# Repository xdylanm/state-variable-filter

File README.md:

# State Variable Filter

The state variable filter is a second order (12dB/oct) filter with low-, high- and band-pass outputs and adjustable resonance. This is a classic filter design that appears in a number of synths, including the Oberheim SEM.

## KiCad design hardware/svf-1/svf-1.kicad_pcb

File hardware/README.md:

Store hardware project and panel here

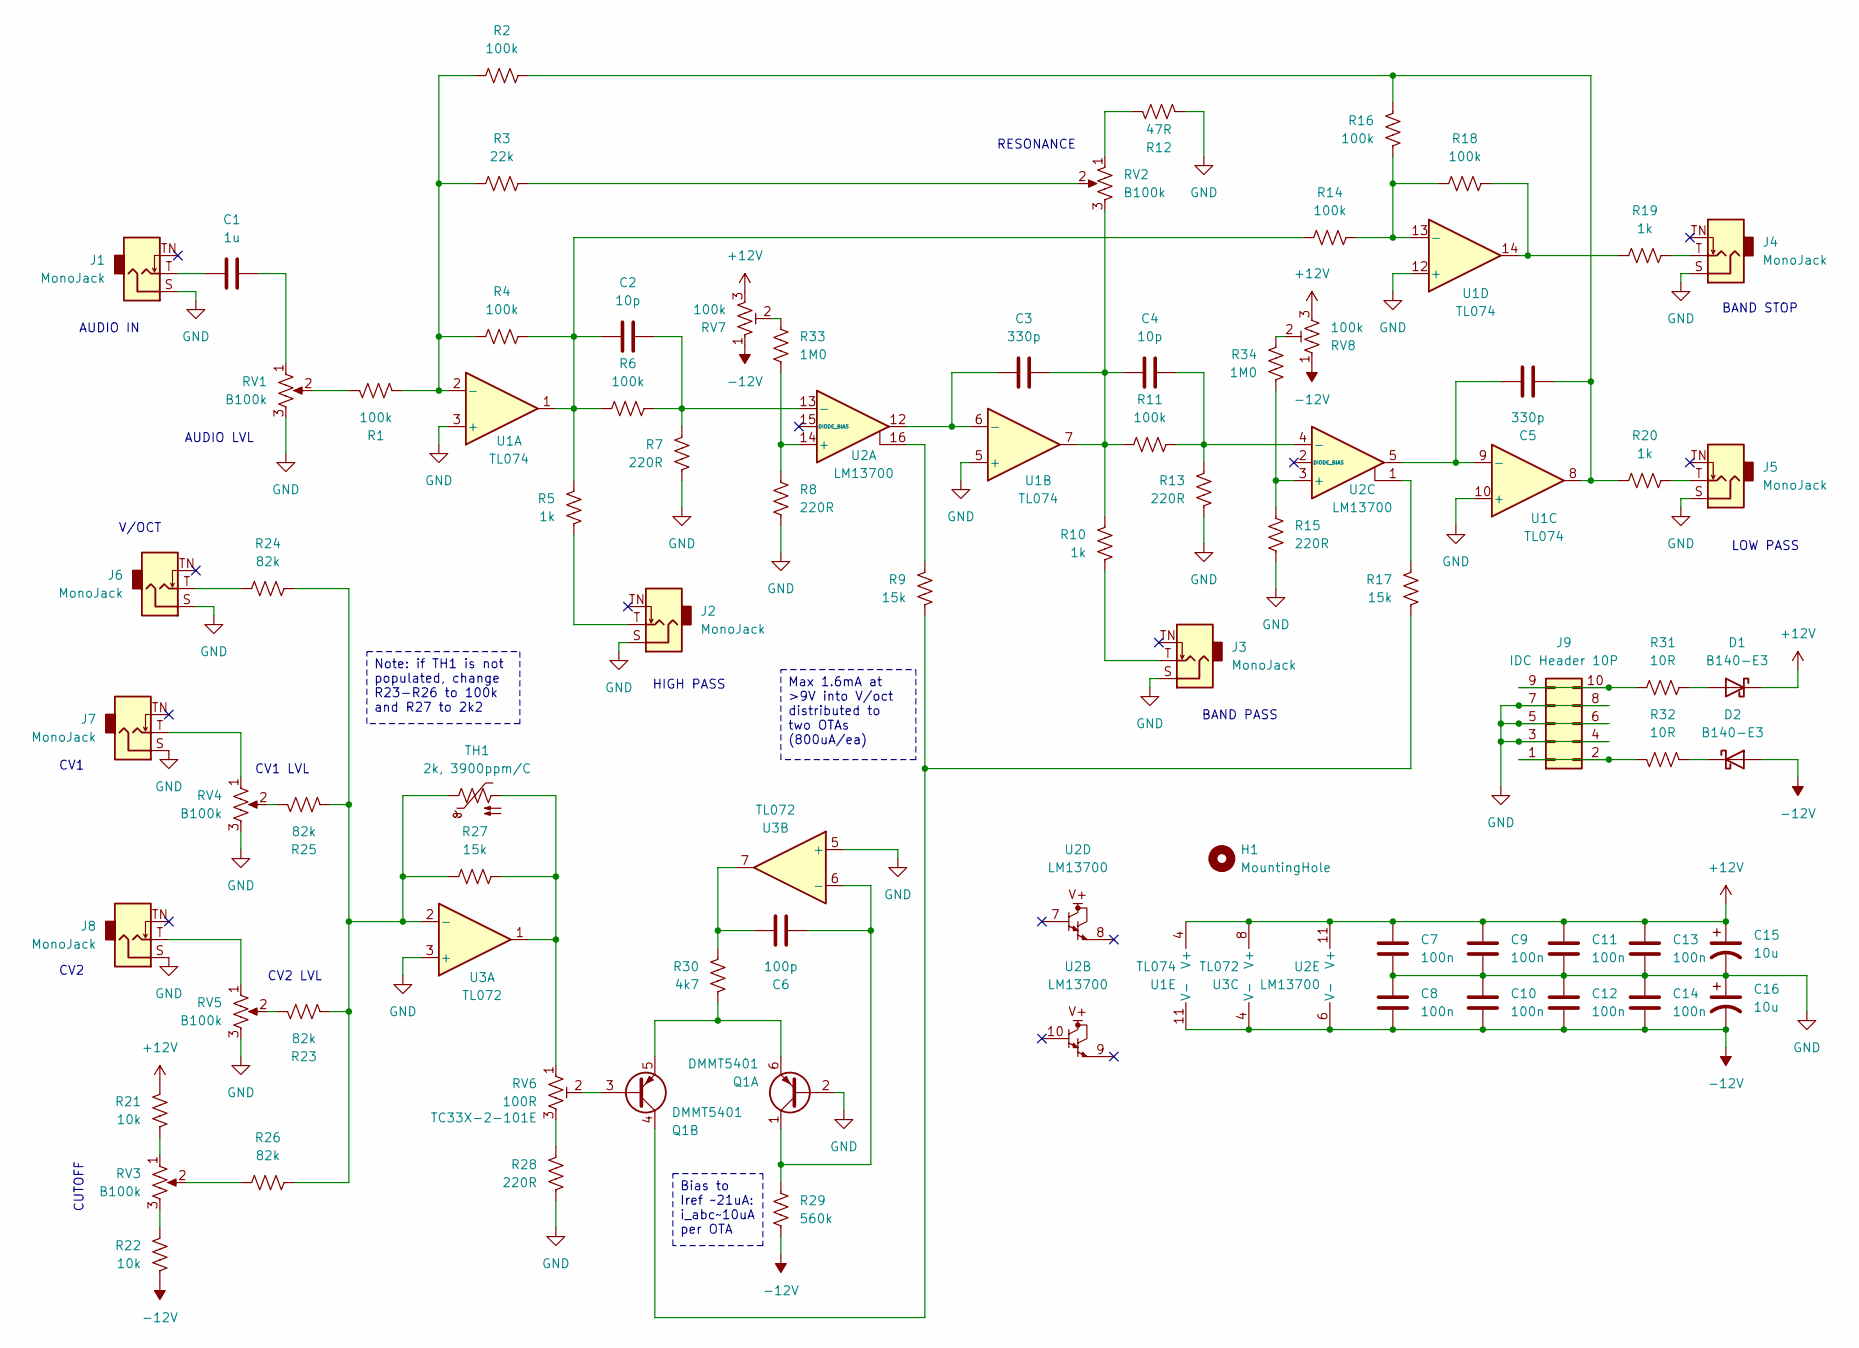
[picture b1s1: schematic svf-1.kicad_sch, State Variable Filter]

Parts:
C1: 1u; C_0805_2012Metric_Pad1.18x1.45mm_HandSolder
C2, C4: 10p; C_0805_2012Metric_Pad1.18x1.45mm_HandSolder
C3, C5: 330p; C_0805_2012Metric_Pad1.18x1.45mm_HandSolder
C6: 100p; C_0805_2012Metric_Pad1.18x1.45mm_HandSolder
C7, C8, C9, C10, C11, C12, C13, C14: 100n; C_0805_2012Metric_Pad1.18x1.45mm_HandSolder
C15, C16: 10u; CP_Radial_D5.0mm_P2.50mm
D1, D2: B140-E3; D_SMA
H1: MountingHole; MountingHole_3.2mm_M3_DIN965
J1, J2, J3, J4, J5, J6, J7, J8: MonoJack; Jack_3.5mm_QingPu_WQP-PJ301M-12_Vertical
J9: IDC Header 10P; IDC-Header_2x05_P2.54mm_Vertical
Q1: DMMT5401; SOT-23-6_Handsoldering
R1, R2, R4, R6, R11, R14, R16, R18: 100k; R_0805_2012Metric_Pad1.20x1.40mm_HandSolder
R3: 22k; R_0805_2012Metric_Pad1.20x1.40mm_HandSolder
R5, R10, R19, R20: 1k; R_0805_2012Metric_Pad1.20x1.40mm_HandSolder
R7, R8, R13, R15, R28: 220R; R_0805_2012Metric_Pad1.20x1.40mm_HandSolder
R9, R17, R27: 15k; R_0805_2012Metric_Pad1.20x1.40mm_HandSolder
R12: 47R; R_0805_2012Metric_Pad1.20x1.40mm_HandSolder
R21, R22: 10k; R_0805_2012Metric_Pad1.20x1.40mm_HandSolder
R23, R24, R25, R26: 82k; R_0805_2012Metric_Pad1.20x1.40mm_HandSolder
R29: 560k; R_0805_2012Metric_Pad1.20x1.40mm_HandSolder
R30: 4k7; R_0805_2012Metric_Pad1.20x1.40mm_HandSolder
R31, R32: 10R; R_0805_2012Metric_Pad1.20x1.40mm_HandSolder
R33, R34: 1M0; R_0805_2012Metric_Pad1.20x1.40mm_HandSolder
RV1, RV2, RV3, RV4, RV5: B100k; Potentiometer_Bourns_PTV09A-1_Single_Vertical_thin
RV6: 100R; Potentiometer_Bourns_TC33X_Vertical
RV7, RV8: 100k; Potentiometer_Bourns_3296W_Vertical
TH1: 2k, 3900ppm/C; R_0805_2012Metric_Pad1.20x1.40mm_HandSolder
U1: TL074; SOIC-14_3.9x8.7mm_P1.27mm
U2: LM13700; SOIC-16_3.9x9.9mm_P1.27mm
U3: TL072; SOIC-8_3.9x4.9mm_P1.27mm

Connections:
+12V: C7.1, C9.1, C11.1, C13.1, C15.1, D1.1 (K), R21.2, RV7.3, RV8.3, U1.4 (V+), U2.11 (V+), U3.8 (V+)
-12V: C8.2, C10.2, C12.2, C14.2, C16.2, D2.2 (A), R22.1, R29.1, RV7.1, RV8.1, U1.11 (V-), U2.6 (V-), U3.4 (V-)
GND: C7.2, C8.1, C9.2, C10.1, C11.2, C12.1, C13.2, C14.1, C15.2, C16.1, J1.S, J2.S, J3.S, J4.S, J5.S, J6.S, J7.S, J8.S, J9.3, J9.4, J9.5, J9.6, J9.7, J9.8, Q1.2 (B1), R7.1, R8.1, R12.2, R13.1, R15.1, R28.1, RV1.3, RV4.3, RV5.3, U1.3 (+), U1.5 (+), U1.10 (+), U1.12 (+), U3.3 (+), U3.5 (+)
unnamed: C1.1, RV1.1
unnamed: C1.2, J1.T
unnamed: C2.2, R4.2, R5.2, R6.1, R14.1, U1.1
unnamed: C3.1, C4.2, R10.2, R11.1, RV2.3, U1.7
unnamed: C5.1, R2.2, R16.2, R20.1, U1.8
unnamed: C6.2, R30.2, U3.7
unnamed: D1.2 (A), R31.2
unnamed: D2.1 (K), R32.2
unnamed: J2.T, R5.1
unnamed: J3.T, R10.1
unnamed: J4.T, R19.2
unnamed: J5.T, R20.2
unnamed: J6.T, R24.1
unnamed: J7.T, RV4.1
unnamed: J8.T, RV5.1
unnamed: J9.1, J9.2, R32.1
unnamed: J9.9, J9.10, R31.1
unnamed: C6.1, Q1.1 (C1), R29.2, U3.6 (-)
unnamed: Q1.5 (E2), Q1.6 (E1), R30.1
unnamed: Q1.3 (B2), RV6.2
unnamed: Q1.4 (C2), R9.1, R17.1
unnamed: R1.1, RV1.2
unnamed: R3.2, RV2.2
unnamed: R9.2, U2.16
unnamed: R12.1, RV2.1
unnamed: R17.2, U2.1
unnamed: R18.2, R19.1, U1.14
unnamed: R21.1, RV3.1
unnamed: R22.2, RV3.3
unnamed: R23.1, RV5.2
unnamed: R25.1, RV4.2
unnamed: R26.1, RV3.2
unnamed: R27.2, RV6.1, TH1.2, U3.1
unnamed: R28.2, RV6.3
unnamed: R33.2, RV7.2
unnamed: R34.2, RV8.2
unnamed: R1.2, R2.1, R3.1, R4.1, U1.2 (-)
unnamed: C3.2, U1.6 (-), U2.12
unnamed: C5.2, U1.9 (-), U2.5
unnamed: R14.2, R16.1, R18.1, U1.13 (-)
unnamed: R8.2, R33.1, U2.14 (+)
unnamed: C2.1, R6.2, R7.2, U2.13 (-)
unnamed: R15.2, R34.1, U2.3 (+)
unnamed: C4.1, R11.2, R13.2, U2.4 (-)
unnamed: R23.2, R24.2, R25.2, R26.2, R27.1, TH1.1, U3.2 (-)

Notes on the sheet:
RESONANCE
CV2 LVL
BAND PASS
CV1 LVL
AUDIO IN
HIGH PASS
BAND STOP
V/OCT
LOW PASS
CUTOFF
CV1
CV2
AUDIO LVL
Max 1.6mA at >9V into V/oct distributed to two OTAs (800uA/ea)
Note: if TH1 is not populated, change R23-R26 to 100k and R27 to 2k2
Bias to Iref ~21uA: i_abc~10uA per OTA

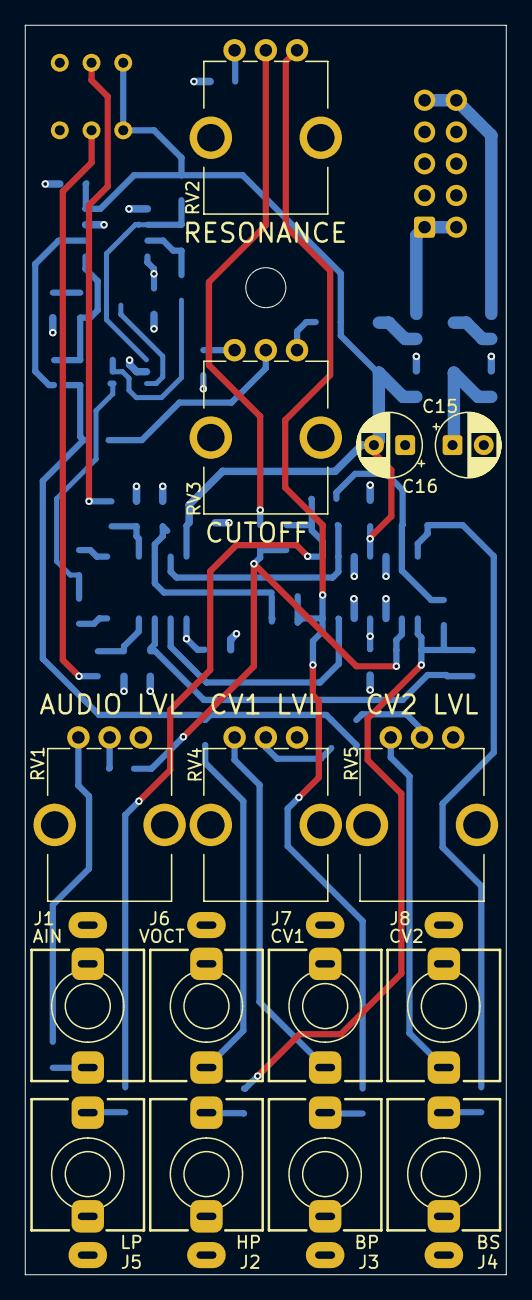
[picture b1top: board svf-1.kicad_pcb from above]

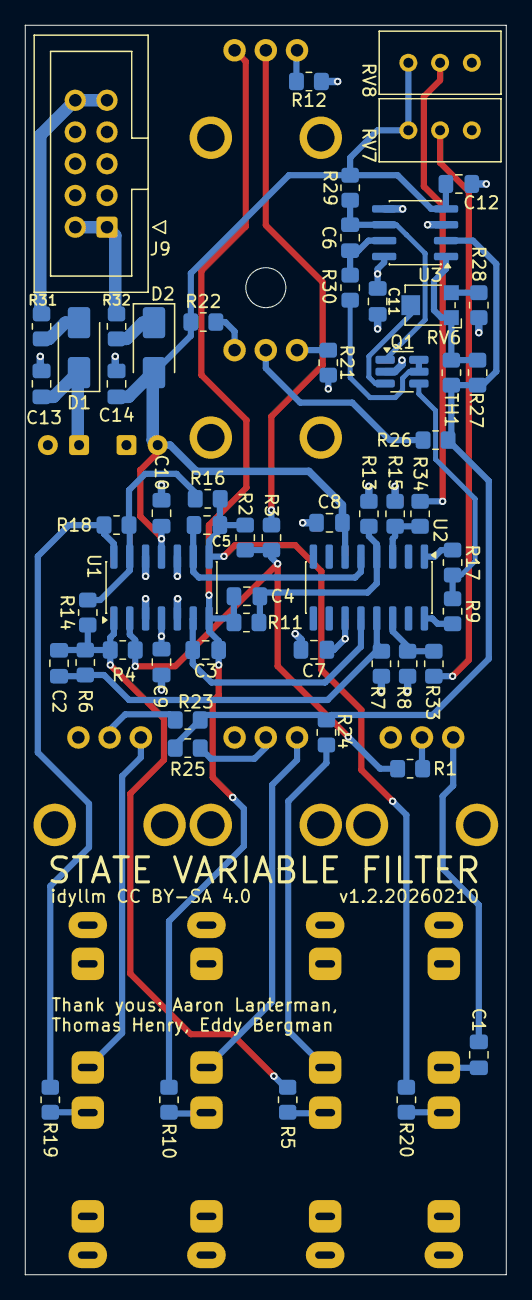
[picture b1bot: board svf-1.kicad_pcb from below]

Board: 4 copper layers, 38.5 x 100.0 mm, 75 parts (59 on the bottom side), 48 nets.

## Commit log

2025-12-14 Initial version of the SVF with docs. Design to gerbers for PCB and verified on breadboard.
2025-12-14 added block diagram source
2025-12-15 Documentation update with 3D renders (added 3D models to footprints for pots)
2025-12-28 Schematic and PBC fix: replace incorrect MMDT5401 (SOT-363) with DMMT5401 (SOT-236) part
2026-01-02 Updated docs and design after building and testing the PCB
2026-01-02 Small doc updates
2026-01-03 Fix CV input pots and Rs
2026-02-10 Fix for flipped PNP wiring
2026-02-10 Updated docs for fix
2026-02-13 Fix pnp wiring (#2)
    * Fix for flipped PNP wiring
    * Updated docs for fix
2026-02-13 Added faceplate and updated docs
2026-02-13 Added images
2026-02-13 Add faceplate (#3)
    * Added faceplate and updated docs
    * Added images

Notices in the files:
hardware/svf-1/svf-1.kicad_pcb:
CC BY-SA 4.0
idyllm CC BY-SA 4.0
